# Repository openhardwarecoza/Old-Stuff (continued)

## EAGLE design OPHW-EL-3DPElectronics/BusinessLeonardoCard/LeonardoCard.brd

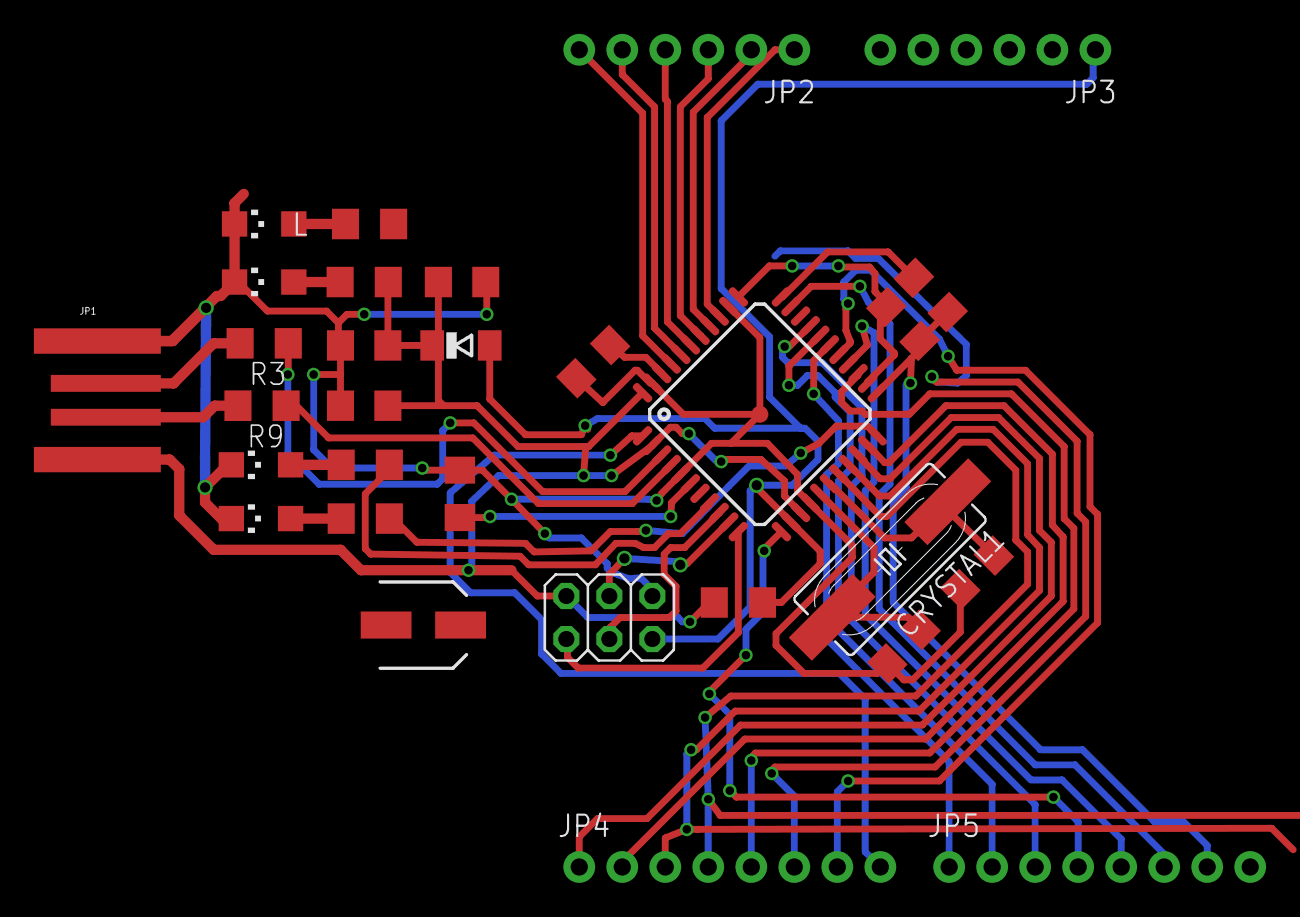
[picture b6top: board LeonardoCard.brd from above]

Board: 2 copper layers, 30 parts (0 on the bottom side), 41 nets.

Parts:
C5, C7: 1uF; C1206
C6, C9, C10, C11: 100n; C1206
C12, C13: 22pF; C1206
C14: 22u; SANYO-OSCON_SMD_B6
CRYSTAL1: CRYSTAL-2PIN
D2: CD1206-S01575; SOD80C
J4: 3x2M; 2X03
JP1: USBPCB; USB-A-PCB
JP2, JP3: 1X06
JP4, JP5: 1X08_NO_SILK
L: green; CHIPLED_1206
ON: blue; CHIPLED_1206
R1, R4: 10K; R1206
R3, R9: 22R; R1206
R5, R6, R7, R8: 1K; R1206
RX: yellow; CHIPLED_1206
TX: yellow; CHIPLED_1206
U1: ATMEGA32U4-XUAU; TQFP44-PAD

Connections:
A0: JP2.1, U1.36
A1: JP2.2, U1.37
A2: JP2.3, U1.38
A3: JP2.4, U1.39
A4: JP2.5, U1.40
A5: JP2.6, U1.41
AREF: C6.1, U1.42
D0/RX: JP4.1, U1.20
D1/TX: JP4.2, U1.21
D2/SDA: JP4.3, U1.19
D3/SCL: JP4.4, U1.18
D4*: JP4.5, U1.25
D5*: JP4.6, U1.31
D6*: JP4.7, U1.27
D7: JP4.8, U1.1
D+: JP1.USB_M, R9.2
D-: JP1.USB_P, R3.2
GND: C5.2, C6.2, C7.2, C9.2, C10.2, C11.2, C12.1, C13.1, C14.-, J4.6, JP1.GND, JP3.4, JP3.5, JP5.7, L.C, ON.C, R4.2, RX.C, TX.C, U1.5, U1.15, U1.23, U1.35, U1.43, U1.P$1
HWB: R4.1, U1.33
IO8: JP5.1, U1.28
IO9*: JP5.2, U1.29
IO10*: JP5.3, U1.30
IO11*: JP5.4, U1.12
IO12*: JP5.5, U1.26
IO13*: JP5.6, R8.1, U1.32
MISO: J4.1, U1.11
MOSI: J4.4, U1.10
unnamed: R7.2, RX.A
unnamed: ON.A, R5.2
unnamed: R6.2, TX.A
unnamed: L.A, R8.2
RD+: R9.1, U1.4
RD-: R3.1, U1.3
RESET: D2.A, J4.5, JP3.1, R1.2, U1.13
RXLED/SS: R7.1, U1.8
SCK: J4.3, U1.9
TXLED: R6.1, U1.22
UCAP: C5.1, U1.6
VCC: C7.1, C9.1, C10.1, C11.1, C14.+, D2.C, J4.2, JP1.5V, JP3.3, R1.1, R5.1, U1.2, U1.14, U1.24, U1.34, U1.44
XTAL1: C13.2, CRYSTAL1.1, U1.17
XTAL2: C12.2, CRYSTAL1.2, U1.16

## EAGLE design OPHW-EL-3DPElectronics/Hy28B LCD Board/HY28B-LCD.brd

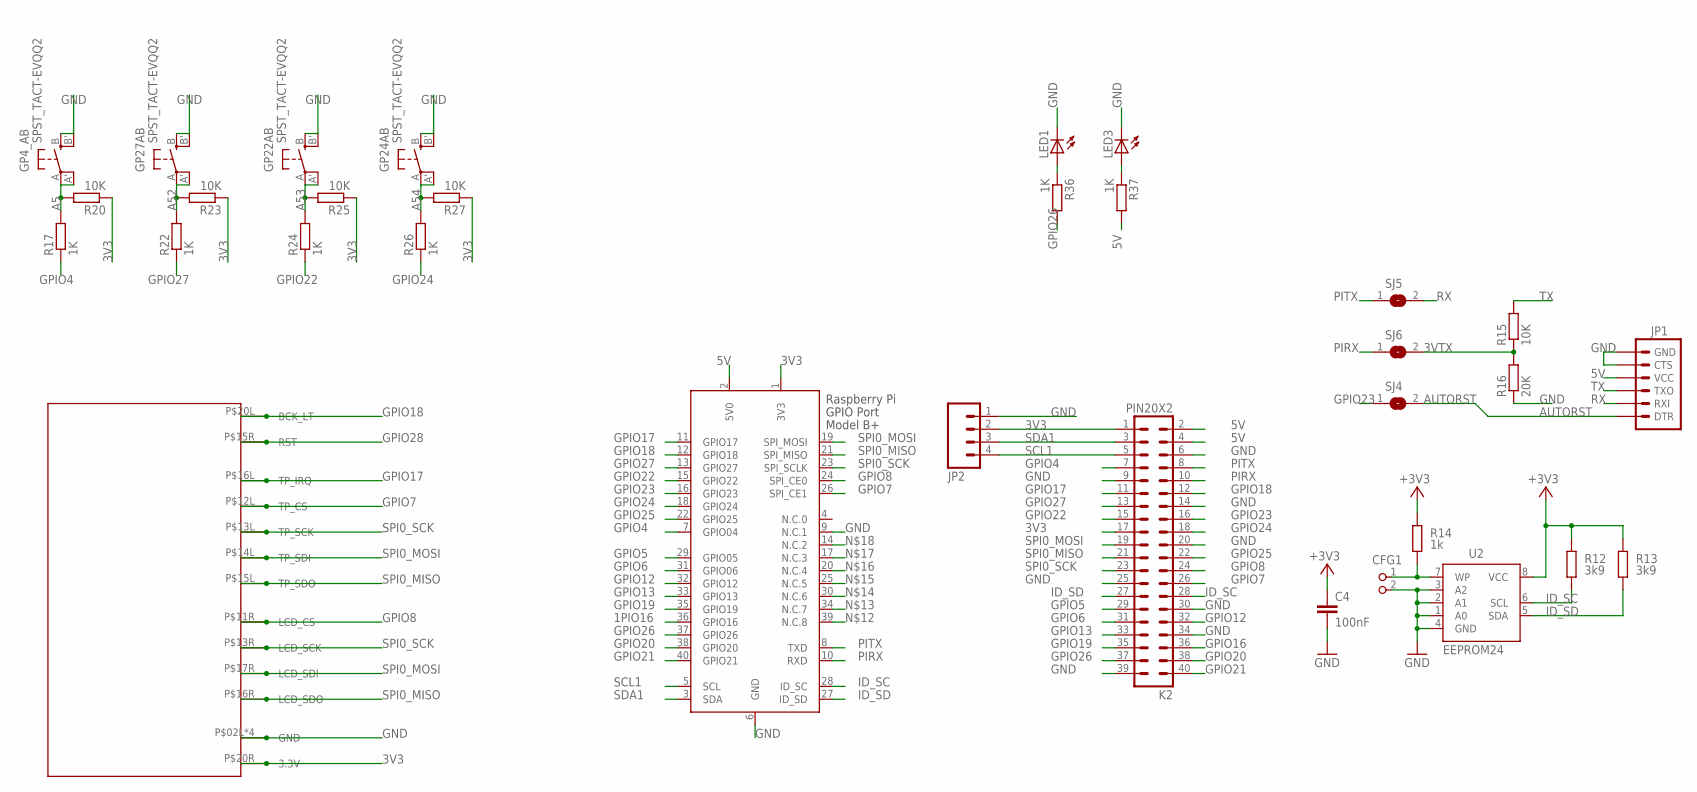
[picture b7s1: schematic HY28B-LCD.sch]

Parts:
C4: 100nF; C1206
CFG1: PIN2_100; PIN_W_2
GP4_AB, GP22AB, GP24AB, GP27AB: SPST_TACT-EVQQ2; EVQ-Q2
JP1: ARDUINO_SERIAL_PROGRAMLOCK; 1X06_LOCK
JP2: M04LOCK; 1X04_LOCK
K2: PIN20X2; PIN_20X2
LED1, LED3: LEDCHIPLED_1206; CHIPLED_1206
R12, R13: 3k9; M1206; TOLERANCE 5%
R14: 1k; M1206; TOLERANCE 5%
R15: 10K; R1206
R16: 20K; R1206
R17, R22, R24, R26: 1K; M1206
R20, R23, R25, R27: 10K; M1206
R36, R37: 1K; R1206
SJ4, SJ5, SJ6: SJ
U2: EEPROM24; SOIC8
U$1: HY28BSTD; HY28B
X1: RASPI_BOARD_B+_F; RASPI_BOARD_B+_FULL

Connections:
1PIO16: X1.36 (GPIO16)
3V3: JP2.2, K2.1, K2.17, R20.1, R23.1, R25.1, R27.1, U$1.P$20R (3.3V), X1.1 (3V3)
3VTX: R15.1, R16.2, SJ6.2
5V: JP1.4 (VCC), K2.2, K2.4, R37.2, X1.2 (5V0)
+3V3: C4.1, R12.2, R13.2, R14.2, U2.8 (VCC)
A5: GP4_AB.A, GP4_AB.A' (P1), R17.2, R20.2
A52: GP27AB.A, GP27AB.A' (P1), R22.2, R23.2
A53: GP22AB.A, GP22AB.A' (P1), R24.2, R25.2
A54: GP24AB.A, GP24AB.A' (P1), R26.2, R27.2
AUTORST: JP1.1 (DTR), SJ4.2
GND: C4.2, CFG1.2, GP4_AB.B (S), GP4_AB.B' (S1), GP22AB.B (S), GP22AB.B' (S1), GP24AB.B (S), GP24AB.B' (S1), GP27AB.B (S), GP27AB.B' (S1), JP1.5 (CTS), JP1.6 (GND), JP2.1, K2.6, K2.9, K2.14, K2.20, K2.25, K2.30, K2.34, K2.39, LED1.C, LED3.C, R16.1, U2.1 (A0), U2.2 (A1), U2.3 (A2), U2.4 (GND), U$1.P$02L (GND), U$1.P$02R (GND), U$1.P$19L (GND), U$1.P$19R (GND), X1.6 (GND), X1.9 (N.C.1)
GPIO4: K2.7, R17.1, X1.7 (GPIO04)
GPIO5: K2.29, X1.29 (GPIO05)
GPIO6: K2.31, X1.31 (GPIO06)
GPIO7: K2.26, U$1.P$12L (TP_CS), X1.26 (SPI_CE1)
GPIO8: K2.24, U$1.P$11R (LCD_CS), X1.24 (SPI_CE0)
GPIO12: K2.32, X1.32 (GPIO12)
GPIO13: K2.33, X1.33 (GPIO13)
GPIO16: K2.36
GPIO17: K2.11, U$1.P$16L (TP_IRQ), X1.11 (GPIO17)
GPIO18: K2.12, U$1.P$20L (BCK_LT), X1.12 (GPIO18)
GPIO19: K2.35, X1.35 (GPIO19)
GPIO20: K2.38, X1.38 (GPIO20)
GPIO21: K2.40, X1.40 (GPIO21)
GPIO22: K2.15, R24.1, X1.15 (GPIO22)
GPIO23: K2.16, SJ4.1, X1.16 (GPIO23)
GPIO24: K2.18, R26.1, X1.18 (GPIO24)
GPIO25: K2.22, X1.22 (GPIO25)
GPIO26: K2.37, R36.2, X1.37 (GPIO26)
GPIO27: K2.13, R22.1, X1.13 (GPIO27)
GPIO28: U$1.P$15R (RST)
ID_SC: K2.28, R12.1, U2.6 (SCL), X1.28 (ID_SC)
ID_SD: K2.27, R13.1, U2.5 (SDA), X1.27 (ID_SD)
unnamed: CFG1.1, R14.1, U2.7 (WP)
unnamed: LED1.A, R36.1
unnamed: LED3.A, R37.1
PIRX: K2.10, SJ6.1, X1.10 (RXD)
PITX: K2.8, SJ5.1, X1.8 (TXD)
RX: JP1.2 (RXI), SJ5.2
SCL1: JP2.4, K2.5, X1.5 (SCL)
SDA1: JP2.3, K2.3, X1.3 (SDA)
SPI0_MISO: K2.21, U$1.P$15L (TP_SDO), U$1.P$16R (LCD_SDO), X1.21 (SPI_MISO)
SPI0_MOSI: K2.19, U$1.P$14L (TP_SDI), U$1.P$17R (LCD_SDI), X1.19 (SPI_MOSI)
SPI0_SCK: K2.23, U$1.P$13L (TP_SCK), U$1.P$13R (LCD_SCK), X1.23 (SPI_SCLK)
TX: JP1.3 (TXO), R15.2

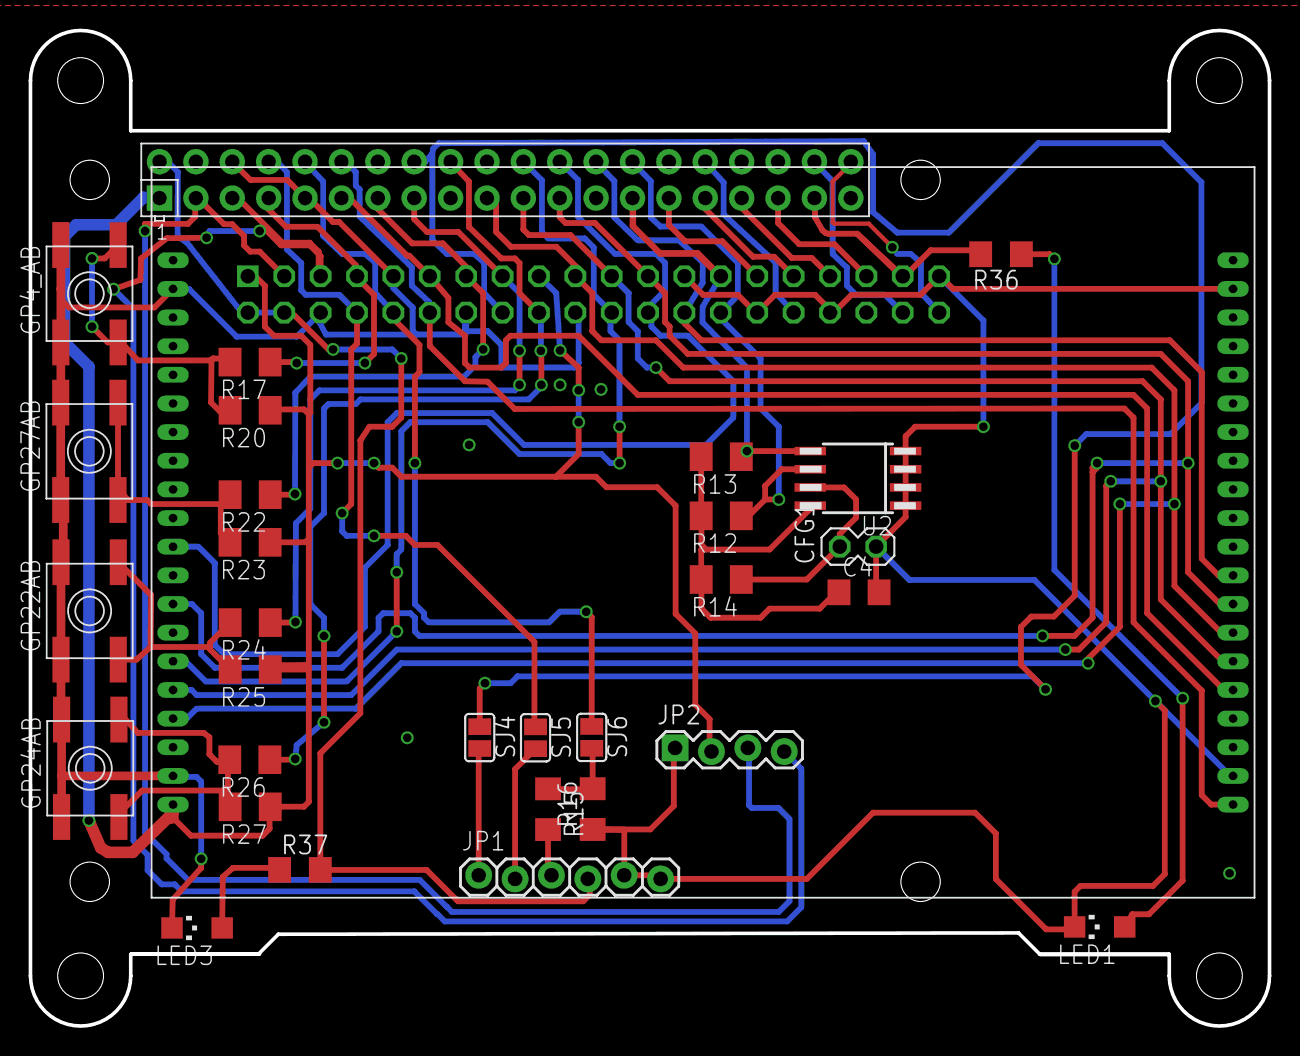
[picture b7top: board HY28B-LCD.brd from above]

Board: 2 copper layers, 86.5 x 69.5 mm, 32 parts (1 on the bottom side), 42 nets.
